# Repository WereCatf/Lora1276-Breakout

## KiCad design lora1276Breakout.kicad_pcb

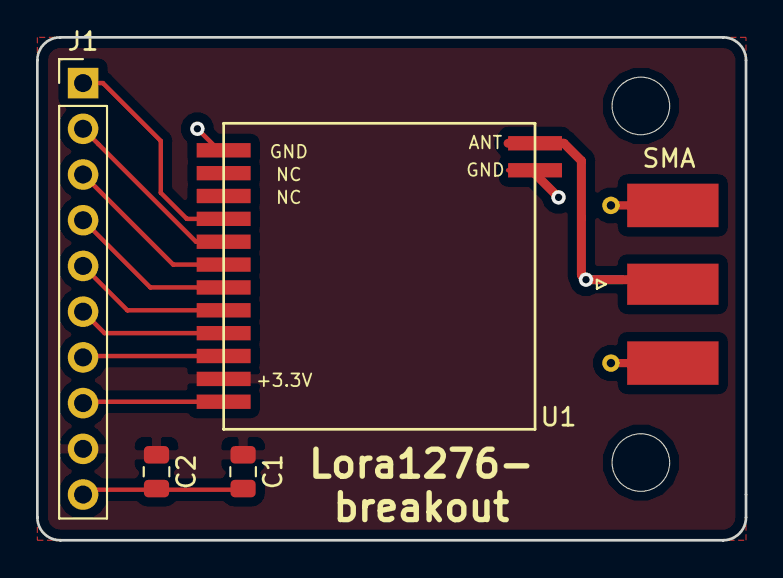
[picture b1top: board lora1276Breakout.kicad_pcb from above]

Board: 2 copper layers, 39.4 x 27.9 mm, 6 parts (1 on the bottom side), 11 nets.

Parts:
C1: 100pF; C_0805_2012Metric
C2: 102pF; C_0805_2012Metric
J1: Conn_01x10_Male; PinHeader_1x10_P2.54mm_Vertical
SMA: Conn_Coaxial; SMA_Molex_73251-1153_EdgeMount_Horizontal
U1: Lora1276_V2.0
u.FL: Conn_Coaxial; U.FL_Hirose_U.FL-R-SMT-1_Vertical

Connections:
+3V3: C1.1, C2.1, J1.9, U1.11
GND: C1.2, C2.2, J1.10, SMA.2, U1.1, U1.14, u.FL.2
unnamed: J1.1, U1.4
unnamed: J1.2, U1.5
unnamed: J1.3, U1.6
unnamed: J1.4, U1.7
unnamed: J1.5, U1.8
unnamed: J1.6, U1.9
unnamed: J1.7, U1.10
unnamed: J1.8, U1.12
unnamed: SMA.1, U1.13, u.FL.1

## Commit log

2018-08-06 Stuffs
2018-09-19 Adjust ant. track-width
